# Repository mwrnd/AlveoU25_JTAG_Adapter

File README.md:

**Work-In-Progress** : [Design manufactured and works](https://github.com/mwrnd/AlveoU25_JTAG_Adapter/releases/download/v0.2-alpha/AlveoU25_JTAG_Adapter_Gerbers.zip) but a footprint is incorrect.

# AlveoU25_JTAG_Adapter

Alveo U25 Debug Connector to Xilinx JTAG, UART, and I2C.

The Adafruit 4471 footprint I used is off by 0.1". Its headers had to be soldered at an angle to work.

I have successfully used it to debug and program an Alveo U25.

The pinout is not available publicly so the signals had to be [traced out](https://github.com/mwrnd/alveo_u25_notes/blob/main/debug_log.md#figuring-out-the-jtag-debug-connector).

## Schematic

## PCB Layout

## Bill Of Materials

**Necessary:**

| Designator(s)    | Part Number          | Quantity | Footprint         | Availability                                                                |
| ---------------- | -------------------- | -------- | ----------------- | --------------------------------------------------------------------------- |
| U1               | MEC8-113-02-L-D-RA1  |        1 | MEC8-113-02-L-D   | [TrustedParts](https://www.trustedparts.com/en/search/MEC8-113-02-L-D-RA1)  |
| J1               | SBH21-NBPN-D07-ST-BK |        1 | SBH21-NBPN-D07-ST | [TrustedParts](https://www.trustedparts.com/en/search/SBH21-NBPN-D07-ST-BK) |
| U5               | 74AVC4T774PW         |        1 | TSSOP-16          | [TrustedParts](https://www.trustedparts.com/en/search/74AVC4T774PW)         |
| R14, R15         | RNCP0603FTD10K0      |        2 | 0603              | [TrustedParts](https://www.trustedparts.com/en/search/RNCP0603FTD10K0)      |
| C4, C5           | CL10B104JB8NNNC      |        2 | 0603              | [TrustedParts](https://www.trustedparts.com/en/search/CL10B104JB8NNNC)      |
| JP1, JP2         | PPTC061LFBN-RC       |        2 | 1x06_2.54mm       | [TrustedParts](https://www.trustedparts.com/en/search/PPTC061LFBN-RC)       |
| x                | Adafruit 4471        |        1 | None - Module     | [TrustedParts](https://www.trustedparts.com/en/part/adafruit/4471)          |

**Optional:**

| Designator(s)    | Part Number          | Quantity | Footprint         | Availability                                                                |
| ---------------- | -------------------- | -------- | ----------------- | --------------------------------------------------------------------------- |
| J5, J7           | PPTC061LFBN-RC       |        2 | 1x06_2.54mm       | [TrustedParts](https://www.trustedparts.com/en/search/PPTC061LFBN-RC)       |
| J3, J4           | PPTC042LFBN-RC       |        2 | 2x04_2.54x2.54mm  | [TrustedParts](https://www.trustedparts.com/en/search/PPTC042LFBN-RC)       |
| J6               | PREC002DAAN-RC       |        1 | 2x02_2.54mm       | [TrustedParts](https://www.trustedparts.com/en/search/PREC002DAAN-RC)       |
| x, x             | STC02SYAN            |          | None - Jumper     | [TrustedParts](https://www.trustedparts.com/en/search/STC02SYAN)            |

## Previous Version

[`v0.1-alpha`](https://github.com/mwrnd/AlveoU25_JTAG_Adapter/releases/tag/v0.1-alpha) was a basic breakout board for the Alveo U25 Debug Connector. It was never manufactured or tested.

Only two components would have been required: [MEC8-113-02-L-D-RA1](https://www.trustedparts.com/en/search/MEC8-113-02-L-D-RA1) and [SBH21-NBPN-D07-ST-BK](https://www.trustedparts.com/en/search/SBH21-NBPN-D07-ST-BK).

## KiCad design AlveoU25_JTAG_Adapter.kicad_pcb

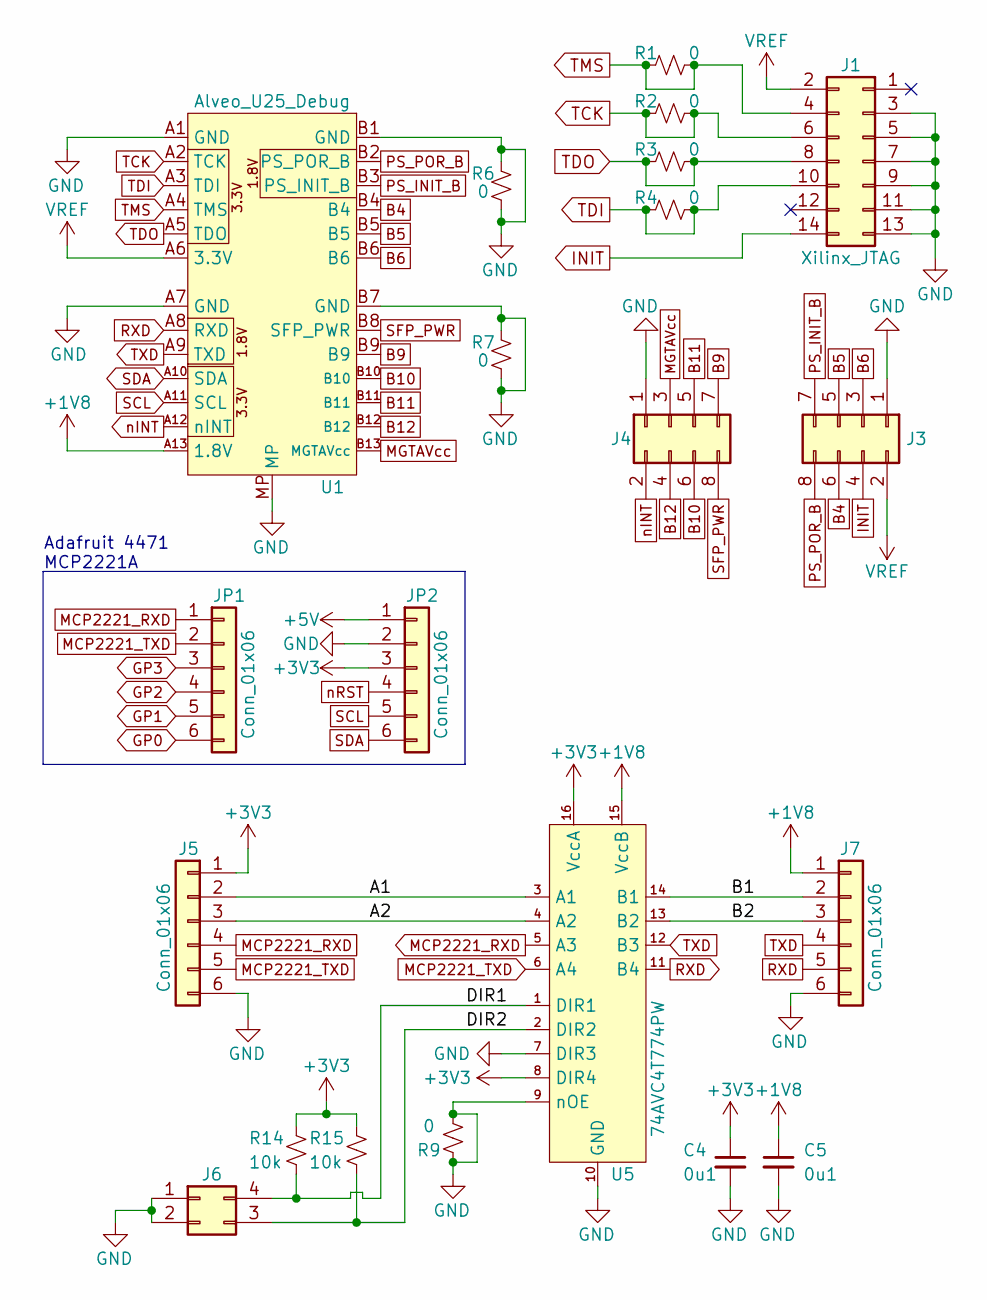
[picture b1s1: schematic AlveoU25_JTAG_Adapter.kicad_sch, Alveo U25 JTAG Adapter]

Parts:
C4, C5: 0u1; C_0603_1608Metric_Pad1.08x0.95mm_HandSolder
J1: Xilinx_JTAG; SBH21-NBPN-D07-ST
J3, J4: Conn_02x04_Odd_Even; PinSocket_2x04_P2.54mm_Vertical
J5, J7: Conn_01x06; PinSocket_1x06_P2.54mm_Vertical
J6: Conn_02x02_Counter_Clockwise; PinSocket_2x02_P2.54mm_Vertical
JP1, JP2: Conn_01x06; PinSocket_1x06_P2.54mm_Vertical
R1, R2, R3, R4, R6, R7, R9: 0; R_0603_1608Metric_Pad0.98x0.95mm_HandSolder
R14, R15: 10k; R_0603_1608Metric_Pad0.98x0.95mm_HandSolder
U1: Alveo_U25_Debug; MEC8-113-02-L-D-RA1
U5: 74AVC4T774PW; TSSOP-16_4.4x5mm_P0.65mm

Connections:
+1V8: C5.1, J7.1, U1.A13 (1.8V), U5.15 (VccB)
+3V3: C4.1, J5.1, JP2.3, R14.1, R15.1, U5.8 (DIR4), U5.16 (VccA)
+5V: JP2.1
+VREF: J1.2, J3.2, U1.A6 (3.3V)
/A1: J5.2, U5.3 (A1)
/A2: J5.3, U5.4 (A2)
/B1: J7.2, U5.14 (B1)
/B2: J7.3, U5.13 (B2)
/DIR1: J6.4, R14.2, U5.1 (DIR1)
/DIR2: J6.3, R15.2, U5.2 (DIR2)
B4: J3.6, U1.B4
B5: J3.5, U1.B5
B6: J3.3, U1.B6
B9: J4.7, U1.B9
B10: J4.6, U1.B10
B11: J4.5, U1.B11
B12: J4.4, U1.B12
GND: C4.2, C5.2, J1.3, J1.5, J1.7, J1.9, J1.11, J1.13, J3.1, J4.1, J5.6, J6.1, J6.2, J7.6, JP2.2, R6.1, R6.2, R7.1, R7.2, R9.1, R9.2, U1.A1 (GND), U1.A7 (GND), U1.B1 (GND), U1.B7 (GND), U1.MP, U5.7 (DIR3), U5.9 (nOE), U5.10 (GND)
GP0: JP1.6
GP1: JP1.5
GP2: JP1.4
GP3: JP1.3
INIT: J1.14, J3.4
MCP2221_RXD: J5.4, JP1.1, U5.5 (A3)
MCP2221_TXD: J5.5, JP1.2, U5.6 (A4)
MGTAVcc: J4.3, U1.B13 (MGTAVcc)
PS_INIT_B: J3.7, U1.B3 (PS_INIT_B)
PS_POR_B: J3.8, U1.B2 (PS_POR_B)
RXD: J7.5, U1.A8 (RXD), U5.11 (B4)
SCL: JP2.5, U1.A11 (SCL)
SDA: JP2.6, U1.A10 (SDA)
SFP_PWR: J4.8, U1.B8 (SFP_PWR)
TCK: J1.6, R2.1, R2.2, U1.A2 (TCK)
TDI: J1.10, R4.1, R4.2, U1.A3 (TDI)
TDO: J1.8, R3.1, R3.2, U1.A5 (TDO)
TMS: J1.4, R1.1, R1.2, U1.A4 (TMS)
TXD: J7.4, U1.A9 (TXD), U5.12 (B3)
nINT: J4.2, U1.A12 (nINT)
nRST: JP2.4

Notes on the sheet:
Adafruit 4471 MCP2221A

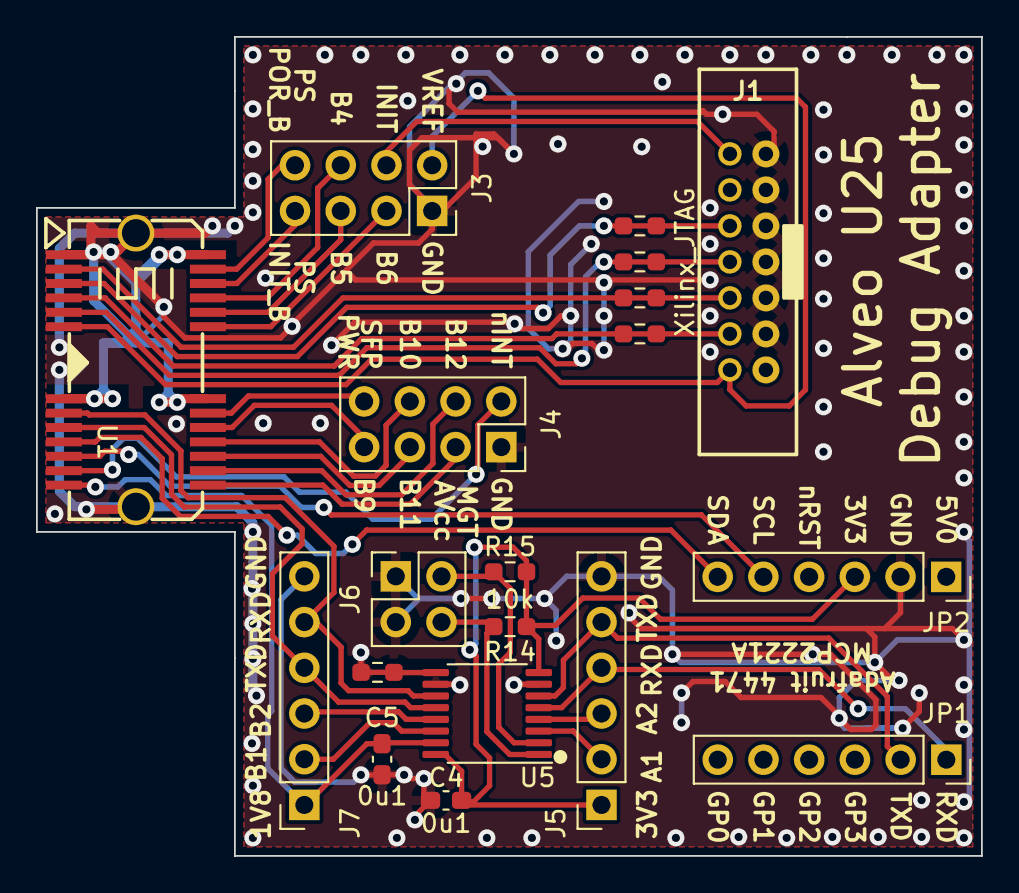
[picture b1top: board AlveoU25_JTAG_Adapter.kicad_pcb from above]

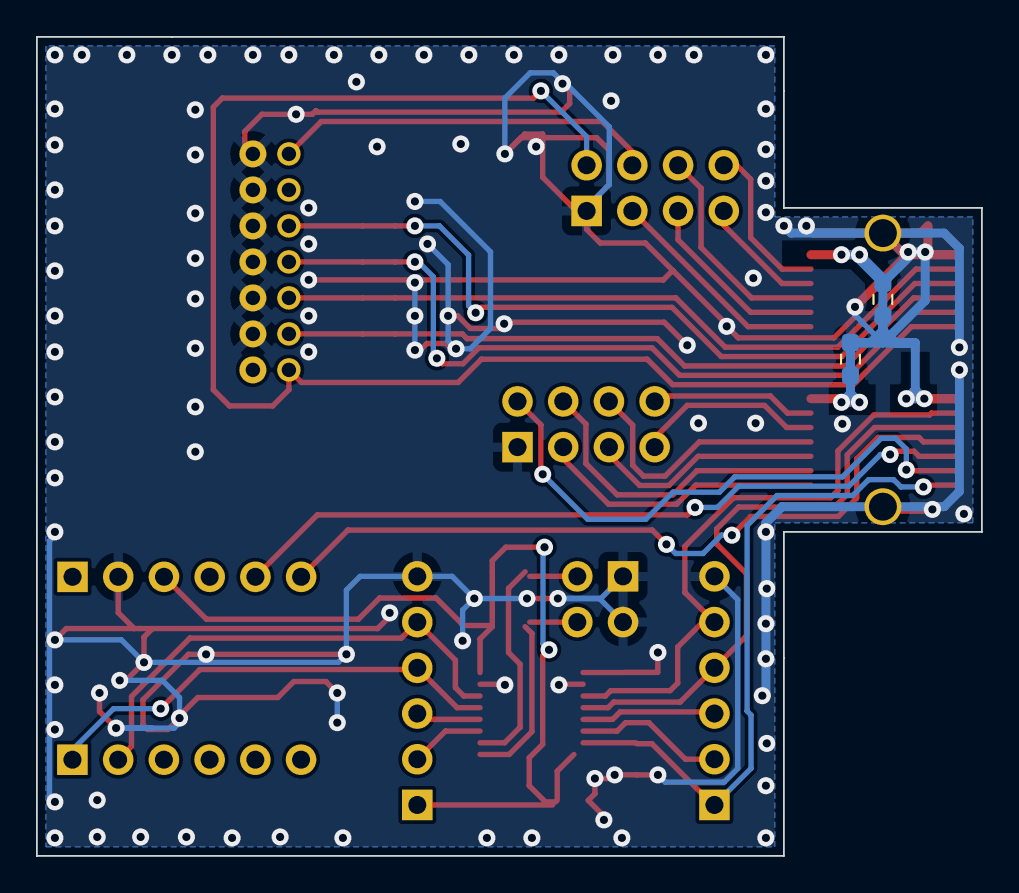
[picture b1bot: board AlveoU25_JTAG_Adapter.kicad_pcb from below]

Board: 2 copper layers, 52.5 x 45.5 mm, 21 parts (2 on the bottom side), 33 nets.

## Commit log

2023-03-16 Symbols and Footprints Finished
2023-04-04 PCB Finished - Just JTAG
2023-04-04 Signal Tracing
2023-05-29 Second Revision
2023-07-11 Design Works!
